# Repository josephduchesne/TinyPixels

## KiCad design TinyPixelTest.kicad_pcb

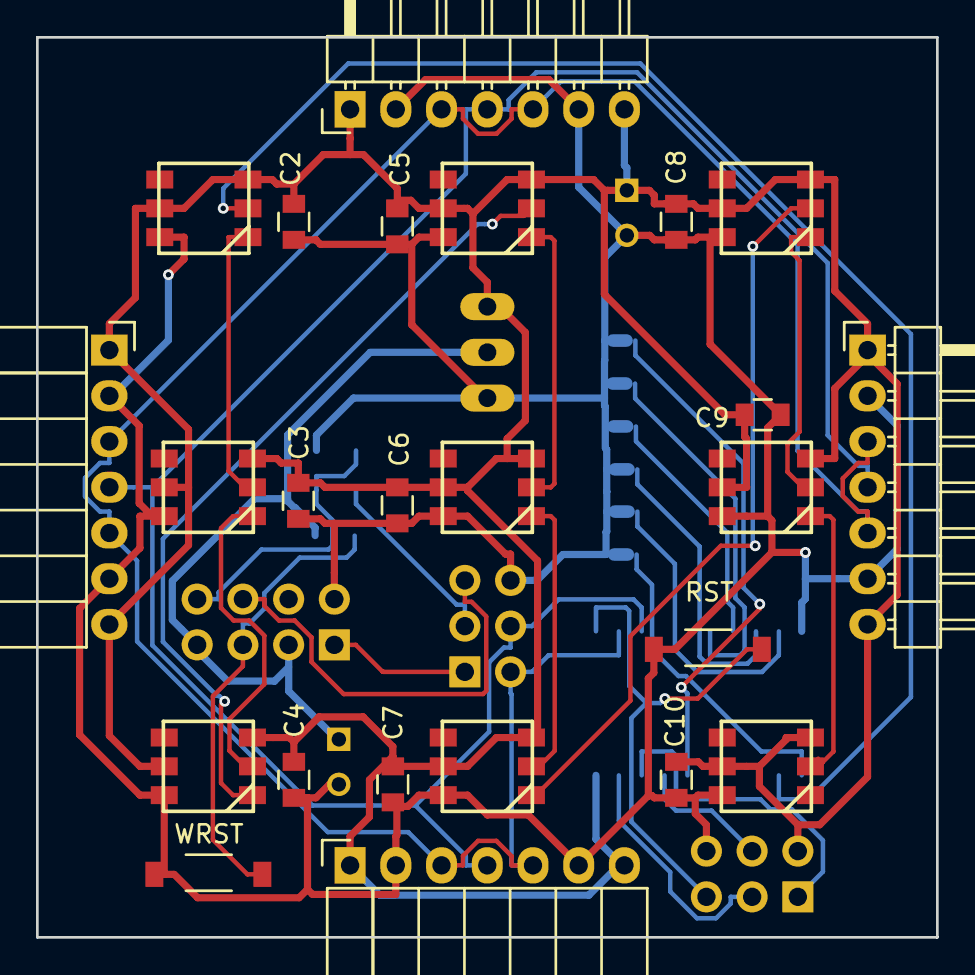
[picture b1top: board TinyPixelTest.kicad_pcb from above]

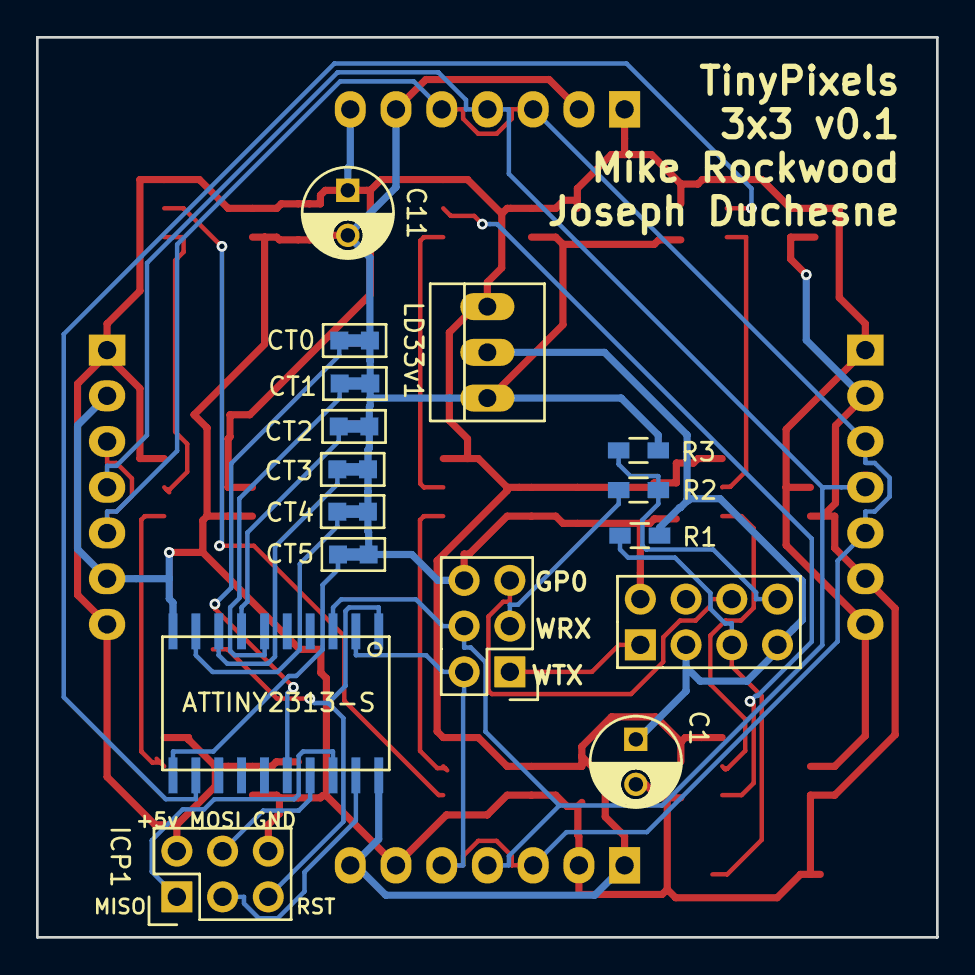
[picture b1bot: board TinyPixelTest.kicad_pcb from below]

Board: 2 copper layers, 50.0 x 50.0 mm, 40 parts (16 on the bottom side), 29 nets.

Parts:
C1, C11: 100uF; C_Radial_D5_L6_P2.5
C2, C3, C4, C5, C6, C7, C8, C9, C10: 100nF; C_0805
CT0, CT1, CT2, CT3, CT4, CT5: CUT-1; CutAway1x2
ESP1: CONN_02X03; Pin_Header_Straight_2x03
ESP-1: ESP-01v090; ESP-01
IC1: ATTINY2313-S; SOIC20-7.4MM
ICP1: CONN_02X03; Pin_Header_Straight_2x03
LD33v1: AP1117; PINHEAD1-3
LED-1, LED-2, LED-3, LED-4, LED-5, LED-6, LED-7, LED-8, LED-9: WS2811-5050
PE3: CONN_01X07; Pin_Header_Angled_1x07
PN1: CONN_01X07; Pin_Header_Angled_1x07
PS2: CONN_01X07; Socket_Strip_Angled_1x07
PW4: CONN_01X07; Socket_Strip_Angled_1x07
R1, R2, R3: R_Small; R_0603_HandSoldering
RST: SW_PUSH; SMD-Switch-3x6
WRST: SW_PUSH; SMD-Switch-3x6

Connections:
+5V: C2.2, C3.2, C4.2, C5.2, C6.2, C7.2, C8.2, C9.2, C10.2, C11.1, IC1.20, ICP1.2, LD33v1.3, LED-1.3, LED-1.5, LED-2.3, LED-2.5, LED-3.3, LED-3.5, LED-4.3, LED-4.5, LED-5.3, LED-5.5, LED-6.3, LED-6.5, LED-7.3, LED-7.5, LED-8.3, LED-8.5, LED-9.3, LED-9.5, PE3.1, PE3.7, PN1.1, PN1.7, PS2.1, PS2.7, PW4.1, PW4.7
GND: C1.2, C2.1, C3.1, C4.1, C5.1, C6.1, C7.1, C8.1, C9.1, C10.1, C11.2, CT0.2, CT1.2, CT2.2, CT3.2, CT4.2, CT5.2, ESP1.6, ESP-1.2, IC1.10, ICP1.6, LD33v1.1, LED-1.6, LED-2.6, LED-3.6, LED-4.6, LED-5.6, LED-6.6, LED-7.6, LED-8.6, LED-9.6, PE3.2, PE3.6, PN1.2, PN1.6, PS2.2, PS2.6, PW4.2, PW4.6, R3.2, RST.1, WRST.1
unnamed: C1.1, ESP-1.3, ESP-1.7, LD33v1.2, R1.1
unnamed: CT0.1, IC1.16
unnamed: CT1.1, IC1.6
unnamed: CT2.1, IC1.7
unnamed: CT3.1, IC1.8
unnamed: CT4.1, IC1.9
unnamed: CT5.1, IC1.11
unnamed: ESP1.2, IC1.2, PE3.3, PE3.5, PN1.3, PN1.5, PS2.3, PS2.5, PW4.3, PW4.5
unnamed: ESP1.3, R2.1
unnamed: ESP1.4, IC1.3, PE3.4, PN1.4, PS2.4, PW4.4
unnamed: ESP1.1, ESP-1.1
unnamed: ESP-1.5, R1.2, WRST.2
unnamed: ESP1.5, ESP-1.6
unnamed: ESP-1.8, R2.2, R3.1
unnamed: IC1.1, ICP1.5, RST.2
unnamed: IC1.12, LED-1.2
unnamed: IC1.17, ICP1.4
unnamed: IC1.18, ICP1.1
unnamed: IC1.19, ICP1.3
unnamed: LED-1.1, LED-2.2
unnamed: LED-2.1, LED-3.2
unnamed: LED-3.1, LED-4.2
unnamed: LED-4.1, LED-5.2
unnamed: LED-5.1, LED-6.2
unnamed: LED-6.1, LED-7.2
unnamed: LED-7.1, LED-8.2
unnamed: LED-8.1, LED-9.2

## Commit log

2016-01-24 :boom::camel: Added .gitattributes & .gitignore files
2016-01-24 Initial Import
2016-01-24 Switched from 4 pin to 7 pin symmetrical connectors
2016-01-24 Fixed wire position
2016-01-24 Uhhh
2016-01-24 Fixed reset switch
2016-01-24 Tesat
2016-01-24 Fixed a connector
    Moved some wires around to make things many more cleaner.
2016-01-24 Created PCB layout
    Added a bunch of files, created the pcb layout and separated all the
    components that were stacked on top of one another.
2016-01-25 Layout
    Put components on board.
2016-01-25 Tweaked pin header 3d model
2016-01-26 Attempted to route
2016-01-26 Added autorouted paths
2016-02-01 Final v0.1 !
2016-02-01 Added Gerbers
2016-04-09 Added ArduinoISP program (3rd party), and RainbowTest (Joseph) with ws2811 library (3rd party)
